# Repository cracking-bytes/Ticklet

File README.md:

> ⚠️ **WARNING**  
> This project has **not yet been tested on real hardware**.  
> The PCB has been designed, and the firmware is complete — but it hasn't been uploaded or verified on a physical board yet.  

# Ticklet
It is a minimalist yet feature-packed hardware timer designed for embedded systems and creative projects. Built using the Seeed Studio **XIAO RP2040**, it utilizes tactile switches, a rotary encoder, an OLED screen, and LEDs — all integrated into a compact PCB designed in KiCad.

## Features

- **Timer Functionality** with Start, Stop, Reset, and Set Time controls  
- **Rotary Encoder** to precisely adjust time in 5-second steps  
- *OLED Display (128x64)** shows live timer status and countdown  
- **LED Indicators** to show current state: idle, paused, or running  
- **Four Mechanical Buttons** for direct control  

---

## Preview

| State       | OLED Display     | LED Behavior        |
|------------|------------------|---------------------|
| Idle        | "Idle" & `00:00` | Only RED ON         |
| Set Mode    | "Set Timer"      | All LEDs OFF        |
| Running     | "Running..."     | Only GREEN ON       |
| Paused      | "Paused"         | Only BLUE ON        |

---

## How It Works

- **Button 1 (GPIO0)** → Start timer  
- **Button 2 (GPIO1)** → Stop timer  
- **Button 3 (GPIO2)** → Reset timer  
- **Button 4 (GPIO3)** → Toggle Set Mode  
- **Rotary Encoder (GPIO4 & GPIO26)** → Add/Subtract time in set mode  
- **OLED (I2C: GPIO6, GPIO7)** → Visual feedback  
- **LEDs (GPIO27, 28, 29)** → State indicators

---

## Pin Mapping

| Component           | Function        | Pin on XIAO RP2040 |
|---------------------|-----------------|---------------------|
| Button 1            | Start           | GPIO0               |
| Button 2            | Stop            | GPIO1               |
| Button 3            | Reset           | GPIO2               |
| Button 4            | Set Mode        | GPIO3               |
| Rotary CLK          | Encoder CLK     | GPIO4               |
| Rotary DT           | Encoder DT      | GPIO26              |
| OLED SDA            | I2C SDA         | GPIO6               |
| OLED SCL            | I2C SCL         | GPIO7               |
| LED 1 (RED)         | Idle Indicator  | GPIO27              |
| LED 2 (BLUE)        | Pause Indicator | GPIO28              |
| LED 3 (GREEN)       | Run Indicator   | GPIO29              |

---

## Firmware

The firmware is written in Arduino C++ using the following libraries:

- `Wire.h` (for I2C communication)
- `Adafruit_GFX.h` (OLED graphics)
- `Adafruit_SSD1306.h` (OLED driver)

👉 Located in: `Firmware/src.ino`

### ⬇️ Installation

1. Install the Arduino IDE
2. Add board support for **[Seeed XIAO RP2040](https://wiki.seeedstudio.com/XIAO-RP2040/)**
3. Install libraries:
   - `Adafruit GFX Library`
   - `Adafruit SSD1306`
4. Connect your XIAO RP2040 via USB-C
5. Upload `src.ino`

---

## PCB Design

- Created using **KiCad 7**
- All symbols and footprints are open source or from KiCad libraries.
- You’ll find:
  - `Kicad files.kicad_pcb` — PCB layout
  - `Kicad files.kicad_sch` — Schematic
  - `Resources/Symbols` — Custom symbols like OLED

---

## Screenshots

**Schematics**
<br>

<br>

**PCB**
<br>

<br>

**3D Front View**
<br>

<br>

**3D Back View**
<br>

<br>

## License

This project is open-source under the [MIT License](LICENSE).  
Feel free to fork, remix, or use it in your own creations!

---

## Author

Bhavika Nagdeo (Cracking Bytes)  
- [GitHub](https://github.com/cracking-bytes)  
- [LinkedIn](https://in.linkedin.com/in/bhavikanagdeo)  
- [Instagram](https://www.instagram.com/cracking.bytes/)  
- [Medium](https://crackingbytes.medium.com/)

## Feedback

If you have any feedback, ideas, or features to suggest, reach out at **bhavikanagdeo83@gmail.com**

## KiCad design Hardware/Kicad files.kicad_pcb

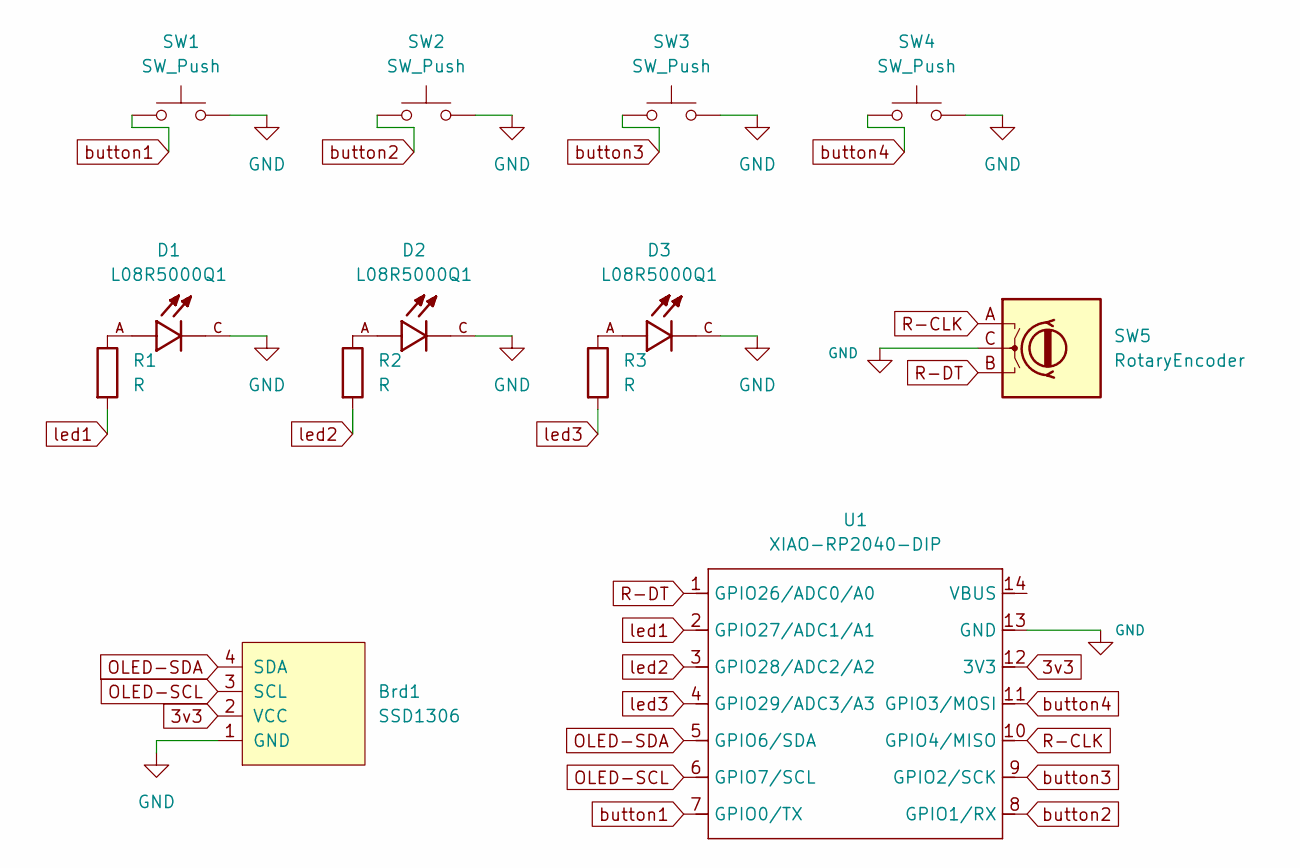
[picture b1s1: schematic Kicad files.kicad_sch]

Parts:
Brd1: SSD1306; 128x64OLED
D1, D2, D3: L08R5000Q1; LEDRD254W57D500H1070; PARTREV NA
R1, R2, R3: R; R_Axial_DIN0204_L3.6mm_D1.6mm_P5.08mm_Horizontal
SW1, SW2, SW3, SW4: SW_Push; SW_Cherry_MX_1.00u_PCB
SW5: RotaryEncoder; RotaryEncoder_Alps_EC11E_Vertical_H20mm
U1: XIAO-RP2040-DIP

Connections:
3v3: Brd1.2 (VCC), U1.12 (3V3)
GND: Brd1.1 (GND), D1.C, D2.C, D3.C, SW1.2, SW2.2, SW3.2, SW4.2, SW5.C, U1.13 (GND)
unnamed: D1.A, R1.1
unnamed: D2.A, R2.1
unnamed: D3.A, R3.1
OLED-SCL: Brd1.3 (SCL), U1.6 (GPIO7/SCL)
OLED-SDA: Brd1.4 (SDA), U1.5 (GPIO6/SDA)
R-CLK: SW5.A, U1.10 (GPIO4/MISO)
R-DT: SW5.B, U1.1 (GPIO26/ADC0/A0)
button1: SW1.1, U1.7 (GPIO0/TX)
button2: SW2.1, U1.8 (GPIO1/RX)
button3: SW3.1, U1.9 (GPIO2/SCK)
button4: SW4.1, U1.11 (GPIO3/MOSI)
led1: R1.2, U1.2 (GPIO27/ADC1/A1)
led2: R2.2, U1.3 (GPIO28/ADC2/A2)
led3: R3.2, U1.4 (GPIO29/ADC3/A3)

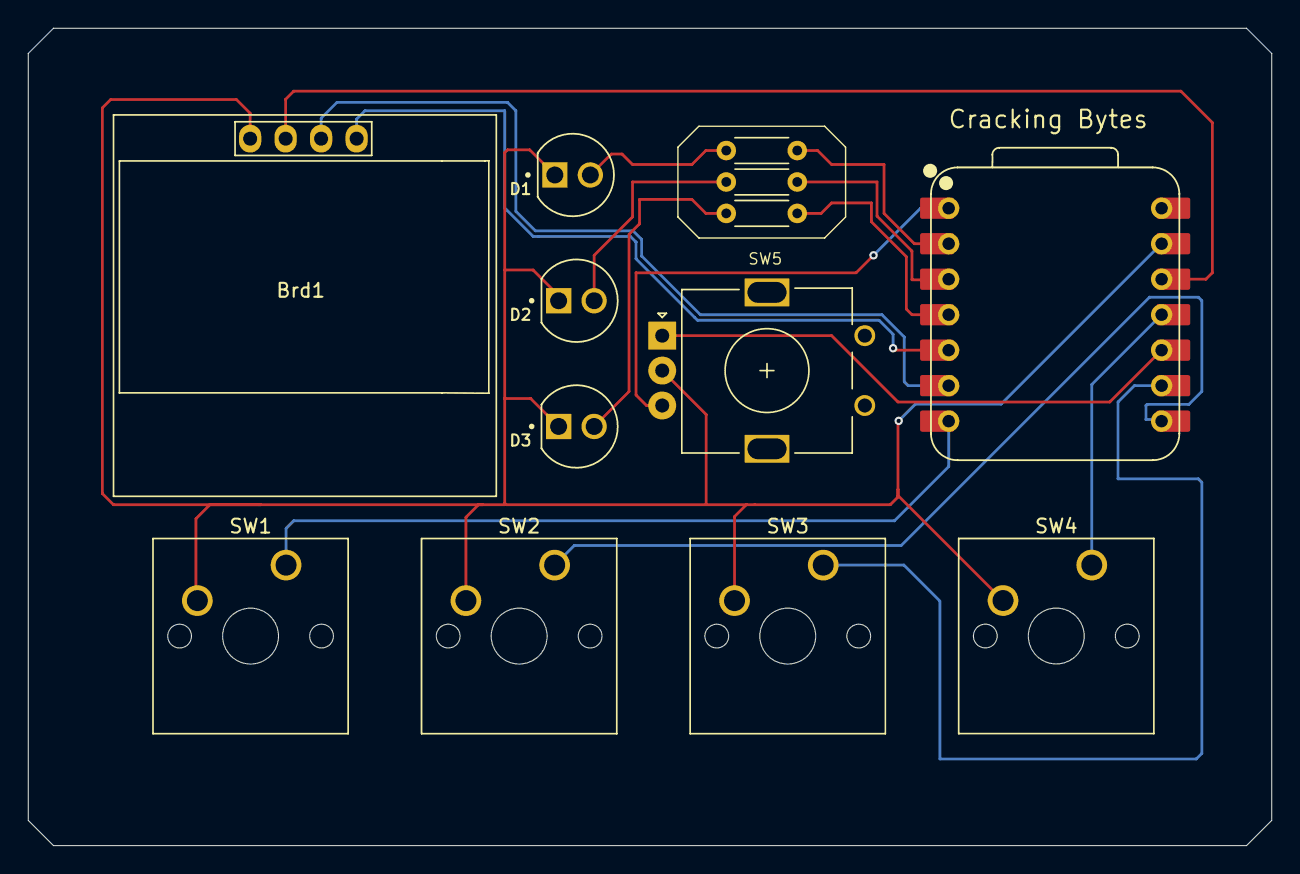
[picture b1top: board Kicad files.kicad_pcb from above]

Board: 2 copper layers, 89.0 x 58.5 mm, 13 parts (0 on the bottom side), 16 nets.

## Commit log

2025-07-04 Added some files to gitignore
2025-07-04 Added Screenshots
2025-07-04 Added Stickers on PCB
